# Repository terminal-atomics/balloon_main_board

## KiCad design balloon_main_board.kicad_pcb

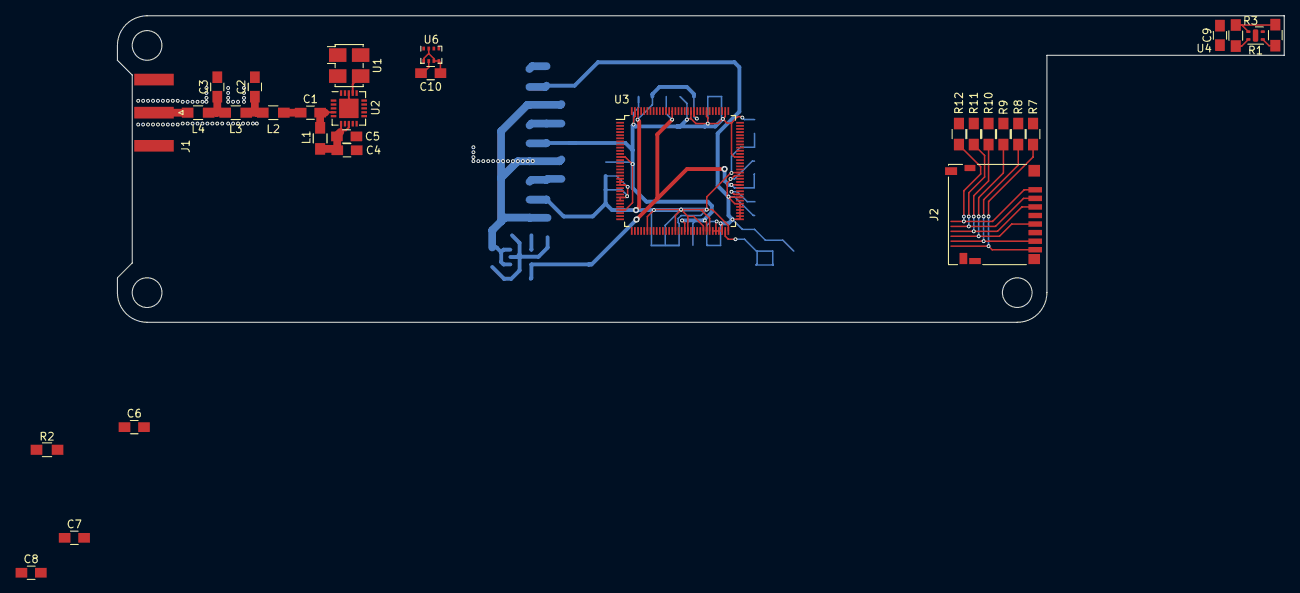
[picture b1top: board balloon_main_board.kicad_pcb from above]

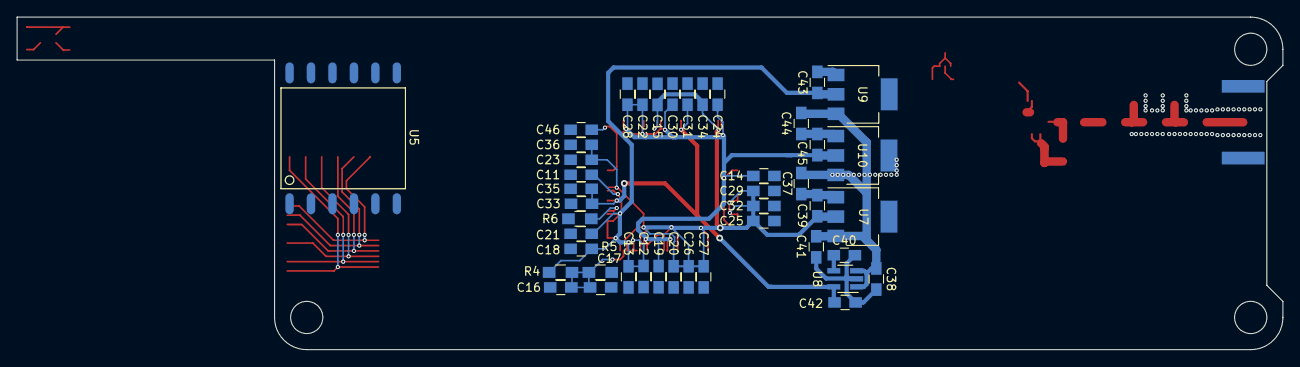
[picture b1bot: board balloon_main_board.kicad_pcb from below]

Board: 2 copper layers, 149.9 x 39.4 mm, 74 parts (44 on the bottom side), 27 nets.

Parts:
C1, C40: 470pF; C_0805_HandSoldering
C2, C3: 27pF; C_0805_HandSoldering
C4, C5, C12, C13, C19, C20, C23, C27, C29: 1uF; C_0805_HandSoldering
C6, C11, C14, C15, C26, C33, C37, C38, C39, C41, C42, C43, C45: 10uF; C_0805_HandSoldering
C7, C9, C10, C16, C17, C18, C21, C22, C24, C25, C28, C31, C32, C34, C35, C36, C46: 100nF; C_0805_HandSoldering
C8, C30: C; C_0805_HandSoldering
C44: 10UF; C_0805_HandSoldering
J1: Conn_Coaxial; SMA_Amphenol_132289_EdgeMount
J2: DM3D-SF; microSD_HC_Hirose_DM3D-SF
L1: 390nH; L_0805_HandSoldering
L2, L4: 56nH; L_0805_HandSoldering
L3: 91nH; L_0805_HandSoldering
R1, R2, R3: 10K; R_0805_HandSoldering
R4, R5: 2K; R_0805_HandSoldering
R6: 240; R_0805_HandSoldering
R7, R8, R9, R10, R11, R12: 47K; R_0805_HandSoldering
U1: SG-8018; Oscillator_SMD_SeikoEpson_SG8002LB-4pin_5.0x3.2mm_HandSolde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
U2: Si4464; QFN-20-1EP_4x4mm_Pitch0.5mm
U3: V3S_QFP-128; TQFP-128_14x14mm_Pitch0.4mm
U4: SHTC3; Sensirion_DFN-4-1EP_2x2mm_P1mm_EP0.7x1.6mm
U5: L80-R
U6: BMP280; Bosch_LGA-8_2x2.5mm_P0.65mm_ClockwisePinNumbering
U7: AZ1117-1.2; SOT-223
U8: MIC5219-3.0YM5; SOT-23-5_HandSoldering
U9: AZ1117-1.8; SOT-223
U10: AZ1117-3.3; SOT-223

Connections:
+1V2: C15.1, C20.1, C23.1, C25.1, C26.1, C27.1, C29.1, C32.1, C34.1, C36.1, C39.1, U3.19, U3.20, U3.21, U3.25, U3.26, U3.38, U3.47, U3.51, U3.56, U3.58, U3.64, U3.80, U3.108, U3.126, U7.2
+1V8: C11.1, C12.1, C13.1, C16.2, C18.1, C21.1, C43.1, R4.1, U3.59, U3.60, U3.61, U3.62, U3.65, U3.66, U3.67, U3.68, U3.69, U3.70, U3.72, U3.79, U9.2
+3V0: C31.1, C33.1, C35.1, C42.1, U3.76, U3.115, U8.5
+3V3: C4.1, C5.2, C6.1, C7.1, C8.1, C9.1, C10.1, C14.1, C19.1, C22.1, C24.1, C28.1, C30.1, C45.1, C46.1, J2.4, L1.2, R1.1, R2.2, R3.1, R7.1, R8.1, R9.1, R10.1, R11.1, R12.1, U1.1, U1.4, U2.6, U2.8, U3.12, U3.29, U3.50, U3.57, U3.85, U3.98, U3.104, U3.109, U3.127, U4.1, U5.4, U6.2, U6.5, U6.6, U6.8, U10.2
+BATT: C37.1, C38.1, C41.1, C44.1, U7.3, U8.1, U8.3, U9.3, U10.3
GND: C2.2, C3.2, C4.2, C5.1, C9.2, C10.2, C11.2, C12.2, C13.2, C14.2, C15.2, C17.1, C18.2, C19.2, C20.2, C21.2, C22.2, C23.2, C24.2, C25.2, C26.2, C27.2, C28.2, C29.2, C30.2, C31.2, C32.2, C33.2, C34.2, C35.2, C36.2, C37.2, C38.2, C39.2, C40.2, C41.2, C42.2, C43.2, C44.2, C45.2, C46.2, J1.2, J2.6, J2.9, R5.1, R6.2, U1.2, U2.1, U2.18, U2.21, U3.116, U4.4, U5.3, U5.12, U6.1, U6.7, U7.1, U8.2, U9.1, U10.1
GPS_RX: U3.39, U5.1
GPS_TX: U3.40, U5.2
HT_SENSE_SCL: R3.2, U4.2
HT_SENSE_SDA: R1.2, U4.3
unnamed: C1.1, L2.1
unnamed: C1.2, L1.1, U2.4
unnamed: C2.1, L2.2, L3.1
unnamed: C3.1, L3.2, L4.1
unnamed: C6.2, C7.2, C8.2
unnamed: C16.1, C17.2, R4.2, R5.2, U3.63, U3.71
unnamed: C40.1, U8.4
unnamed: J1.1, L4.2
unnamed: R2.1, U5.10
unnamed: R6.1, U3.73
unnamed: U1.3, U2.17
SD_CLK: J2.5, R9.2, U3.105
SD_CMD: J2.3, R10.2, U3.103
SD_DAT0: J2.7, R8.2, U3.106
SD_DAT1: J2.8, R7.2, U3.107
SD_DAT2: J2.1, R12.2, U3.101
SD_DAT3: J2.2, R11.2, U3.102
